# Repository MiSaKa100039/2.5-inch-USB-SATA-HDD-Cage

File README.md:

# ***2.5寸USB-SATA硬盘笼***

## <u>视频链接:[B站视频--功能演示及介绍](https://www.bilibili.com/video/BV1YCw5eoERG/?vd_source=5028cf5016d7ed990ad38551eb4883cf)</u>

## 项目简介:

本项目采用JMS578作为usb-sata桥,JMB575端口倍增的方案,实现usb到多个sata硬盘的通信

## 项目参数:

DC12v电源输入,jms578内置3.3v的ldo和buck控制器,因此只需考虑jmb575的3.3v和1.2v电压供电.
12v输入进来后通过tps54335a降压到5v,再使用mp9148双路buck降压输出3.3和1.2给jmb575供电

但是考虑到tps54335a的封装有点不好焊接,隧将其改为了中兴zxdn10的电源模块
和主机间连接采用Type-B接口,相对来说更为牢固.接口速度为USB3.0 5Gpbs,但是usb后面级联sata的方案对于硬盘的随机读写性能有较大的损失,所以对此在意的可以考虑其他方案(机械硬盘用户无视此条)

## 注意事项

1.在usb接口和dc电源接口的地方,请用钳子剪掉突出来的引脚,避免接触到硬盘.

2.先焊接电源部分,上电电压正常后再焊接芯片,以免烧毁芯片

3.jms578的晶振为30mhz,jmb575为25mhz

4.固件默认休眠时间为10min,若需更长时间或者关闭休眠,可以使用附件中的软件修改

5.由于最后一次修改工程后没能保存,所以附件中的ib0m和实际有区别,就是风扇接口位置不同.

6.电源功率的大小取决于你的硬盘功率

7.flash大部分都兼容,不确定就买p25d40h,便宜好用.

## 组装流程

背后的散热风扇为12v5010的风扇,主板上有一颗电阻位,可以选择合适大小的电阻来调节风扇转速,一般情况下直接短接即可

## 实物图

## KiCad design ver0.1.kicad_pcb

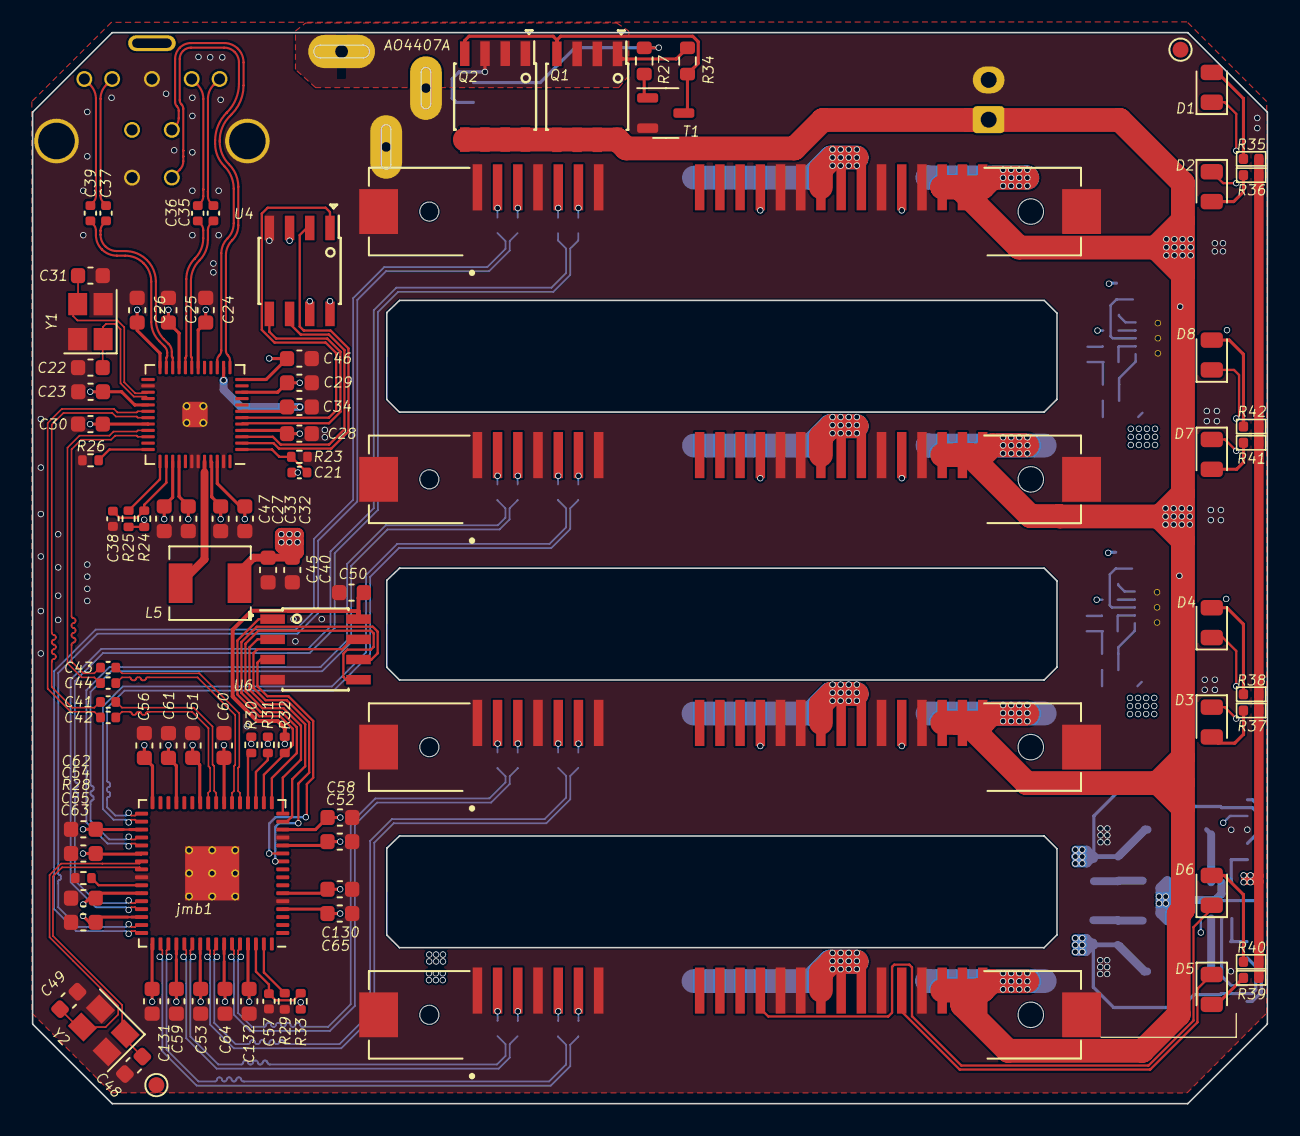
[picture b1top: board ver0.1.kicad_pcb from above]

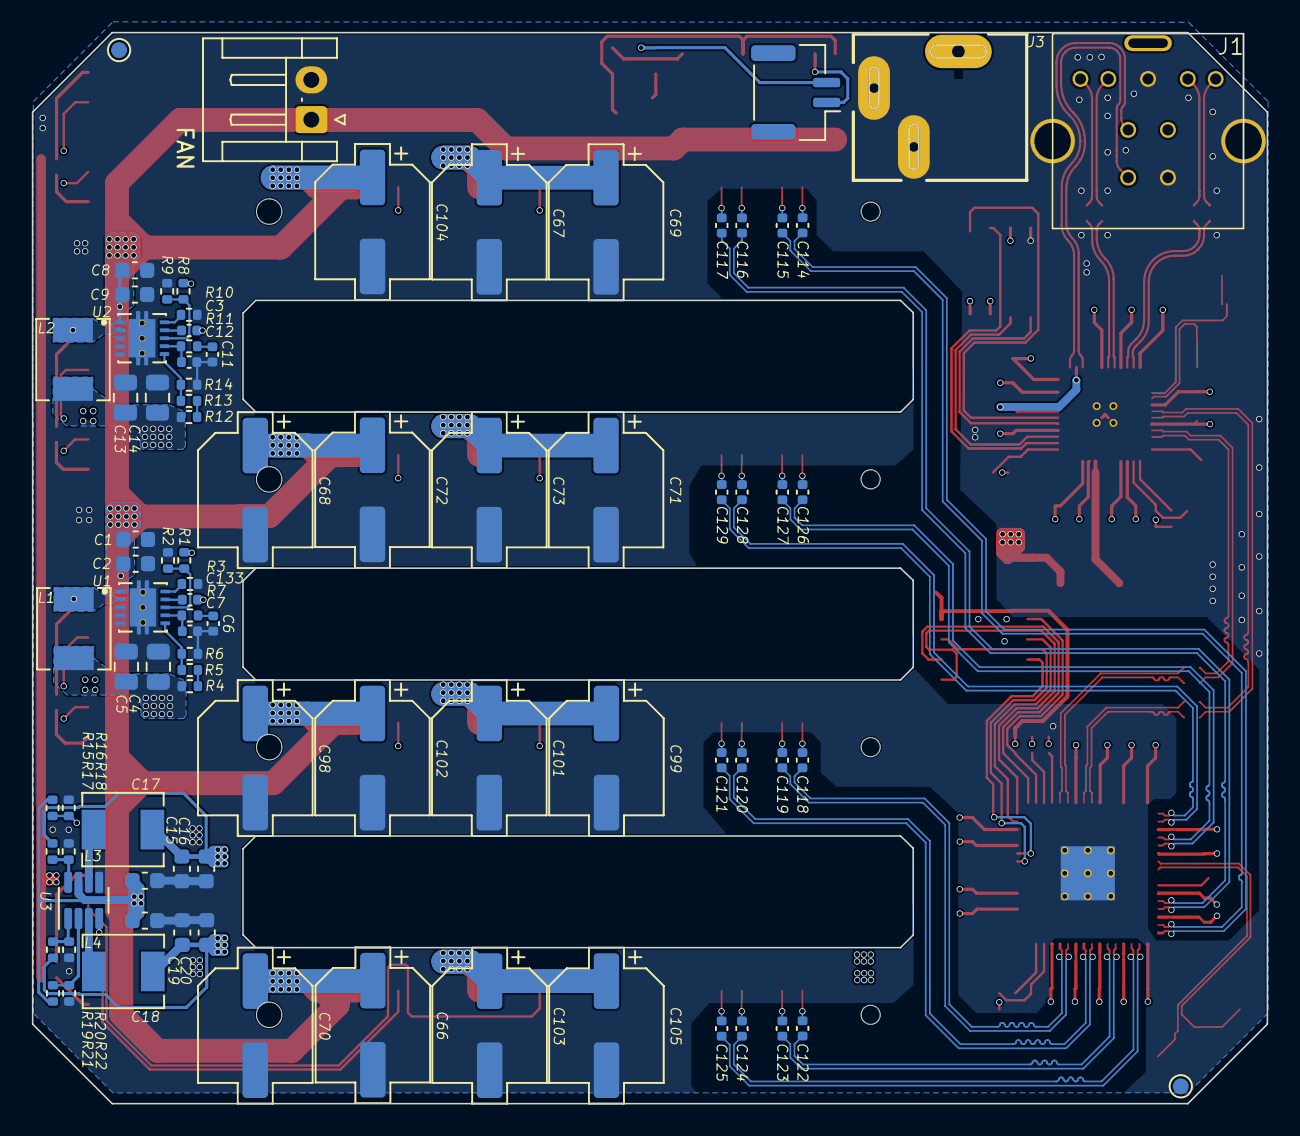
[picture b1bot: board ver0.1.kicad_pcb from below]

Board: 4 copper layers, 77.6 x 67.3 mm, 178 parts (86 on the bottom side), 124 nets.

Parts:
C1, C8, C15, C16, C19, C20, C40: 10uF; C_0603_1608Metric
C2, C9, C45: 0.1uF; C_0603_1608Metric
C3, C133: 0.1uF; C_0402_1005Metric
C4, C5, C13, C14: 47uF; C_0805_2012Metric
C6, C11: 0.012uF; C_0402_1005Metric
C7, C12: 120pF; C_0402_1005Metric
C17, C18: 22uF; C_0603_1608Metric
C21, C38, C57: 1uF; C_0402_1005Metric
C22, C31: 33pF; C_0603_1608Metric
C23, C24, C25, C26, C27, C28, C29, C30, C32, C33, C34, C46, C47, C50, C51, C52, C53, C54, C55, C56, C58, C59, C60, C61, C62, C63, C64, C65, C130, C131, C132: 100nF; C_0603_1608Metric
C35, C36: 100nF; C_0402_1005Metric
C37, C39: 0R; C_0402_1005Metric
C41, C42, C43, C44, C114, C115, C116, C117, C118, C119, C120, C121, C122, C123, C124, C125, C126, C127, C128, C129: 10nF; C_0402_1005Metric
C48, C49: 25pF; C_0603_1608Metric
C66, C67, C68, C69, C70, C71, C72, C73: 270uF; CP_Elec_6.3x5.4
C98, C99, C101, C102, C103, C104, C105: 22uF; CP_Elec_6.3x5.3
D1, D2, D3, D4, D5, D6, D7, D8: LED; LED_0805_2012Metric
FAN: fan2; JST_EH_S2B-EH_1x02_P2.50mm_Horizontal
FID1, FID2, FID3, FID4: Fiducial; TestPoint_Pad_D1.0mm
J1: USB 3.1 B; USB B 母座 直立
J2: SWITCH; JST_GH_BM02B-GHS-TBT_1x02-1MP_P1.25mm_Vertical
J3: dc 5.5mm; DC socket 5.5mm
J4, J5, J6, J7: SATA硬盘插头; SATA 29pin smd
L1, L2: 15uH; L_Chilisin_BMRA00040420
L3: 1uH; L_Chilisin_BMRA00040420
L4: 2uH; L_Chilisin_BMRA00040420
L5: 4.7uH; L_Chilisin_BMRA00040420
Q1, Q2: AO4407A; SOIC-8_3.9x4.9mm_Pitch1.27mm
R1, R8: 220k; R_0402_1005Metric
R2, R9: 43.2K; R_0402_1005Metric
R3, R10: 143K; R_0402_1005Metric
R4, R12: 51.1R; R_0402_1005Metric
R5, R13, R15, R21: 100k; R_0402_1005Metric
R6, R14: 19.1K; R_0402_1005Metric
R7, R11: 3.74K; R_0402_1005Metric
R16, R22: 43k; R_0402_1005Metric
R17, R19: 600K; R_0402_1005Metric
R18: 712K; R_0402_1005Metric
R20: 140K; R_0402_1005Metric
R23: 100K; R_0402_1005Metric
R24: 330K; R_0402_1005Metric
R25, R29, R30, R31, R32: 4.7K; R_0402_1005Metric
R26: 12K; R_0402_1005Metric
R27: 200Re; R_0603_1608Metric
R28: 12k; R_0402_1005Metric
R33: 10k; R_0402_1005Metric
R34: 4k; R_0603_1608Metric
R35, R36, R37, R38, R39, R40, R41, R42: 2k; R_0402
T1: T-BJT-NPN; SOT-23-3
U1, U2: TPS54335A; TPS54335ADRCR
U3: SOT-23-8
U4, U6: SOIC-8_3.9x4.9mm_Pitch1.27mm
U5: QFN-48-1EP_6x6mm_P0.4mm_EP4.2x4.2mm_ThermalVias
Y1, Y2: Crystal_GND24_Small; Crystal_SMD_Abracon_ABM8AIG-4Pin_3.2x2.5mm
jmb1: QFN-64-1EP_9x9mm_P0.5mm_EP3.4x3.4mm_ThermalVias

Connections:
+1V2: C15.2, C16.2, C58.2, C59.2, C60.2, C61.2, C62.2, C63.2, C64.2, C65.2, L3.1, R17.2, jmb1.4 (DV1.2), jmb1.14 (DV1.2), jmb1.23 (AV1.2), jmb1.29 (AV1.2), jmb1.35 (AV1.2), jmb1.46 (AV1.2), jmb1.52 (AV1.2), jmb1.58 (AV1.2)
+3V3: C19.2, C20.2, C50.2, C51.2, C52.2, C53.2, C54.2, C55.2, C56.2, C130.2, C131.2, C132.2, L4.2, R19.2, R30.2, R31.2, R32.2, R33.2, R35.1, R36.1, R37.1, R38.1, R39.1, R40.1, R41.1, R42.1, U6.8 (VCC), jmb1.6 (DV3.3), jmb1.12 (DV3.3), jmb1.26 (AV3.3), jmb1.32 (AV3.3), jmb1.38 (AV3.3), jmb1.43 (AV3.3), jmb1.49 (AV3.3), jmb1.55 (AV3.3), jmb1.61 (AV3.3)
+5V: C4.1, C5.1, C13.1, C14.1, C17.2, C18.2, C67.1, C69.1, C71.1, C73.1, C99.1, C101.1, C103.1, C105.1, J4.P7, J4.P8, J4.P9, J5.P7, J5.P8, J5.P9, J6.P7, J6.P8, J6.P9, J7.P7, J7.P8, J7.P9, L1.2, L2.2, R4.1, R12.1, R15.2, R21.2, U3.7 (IN)
/AGPIO0: U6.6 (SCLK), jmb1.17 (ZGPIO0)
/AGPIO1: U6.5 (SI), jmb1.16 (ZGPIO1)
/AGPIO2: U6.2 (SO), jmb1.15 (ZGPIO2)
/AGPIO3: U6.3 (WP#), jmb1.11 (ZGPIO3)
/AGPIO4: U6.7 (HOLD#), jmb1.10 (ZGPIO4)
/AGPIO12: R29.1, jmb1.63 (ZGPIO12)
/AGPIO13: R31.1, jmb1.19 (ZGPIO13)
/AGPIO14: R32.1, U6.1 (CS#), jmb1.18 (ZGPIO14)
/ARESETn: C57.1, R33.1, jmb1.62 (XRSTN)
/AREXT: R28.1, jmb1.42 (AREXT)
/ARXN0: C116.2, jmb1.45 (ARXN0)
/ARXN1: C120.2, jmb1.57 (ARXN1)
/ARXN2: C124.2, jmb1.51 (ARXN2)
/ARXN3: C128.2, jmb1.34 (ARXN3)
/ARXP0: C117.2, jmb1.44 (ARXP0)
/ARXP1: C121.2, jmb1.56 (ARXP1)
/ARXP2: C125.2, jmb1.50 (ARXP2)
/ARXP3: C129.2, jmb1.33 (ARXP3)
/ATESTn: R30.1, jmb1.20 (XTSTN)
/ATXN0: C115.2, jmb1.47 (ATXN0)
/ATXN1: C119.2, jmb1.59 (ATXN1)
/ATXN2: C123.2, jmb1.53 (ATXN2)
/ATXN3: C127.2, jmb1.36 (ATXN3)
/ATXP0: C114.2, jmb1.48 (ATXP0)
/ATXP1: C118.2, jmb1.60 (ATXP1)
/ATXP2: C122.2, jmb1.54 (ATXP2)
/ATXP3: C126.2, jmb1.37 (ATXP3)
/AXIN: C49.1, Y2.3, jmb1.39 (AXIN)
/AXOUT: C48.2, Y2.1, jmb1.40 (AXOUT)
/DAS1: D2.1 (K), J4.P11
/DAS2: D3.1 (K), J5.P11
/DAS3: D5.1 (K), J6.P11
/DAS4: D7.1 (K), J7.P11
/GPIO0: U4.2 (SO), U5.2 (GPIO0)
/GPIO1: U4.6 (SCLK), U5.3 (GPIO1)
/GPIO2: U4.5 (SI), U5.5 (GPIO2)
/GPIO3: U4.1 (CS#), U5.6 (GPIO3)
/HOT1: D1.1 (K), J4.P4
/HOT2: D4.1 (K), J5.P4
/HOT3: D6.1 (K), J6.P4
/HOT4: D8.1 (K), J7.P4
/HSD0+: J1.3 (D+), U5.15 (DP)
/HSD0-: J1.2 (D-), U5.13 (DM)
/LXO: L5.1, U5.44 (LXO)
/RST: C38.1, R24.2, U5.38 (RST#)
/RX_N: C41.1, U5.31 (RXN)
/RX_P: C42.1, U5.30 (RXP)
/SSRX0+: C39.1, J1.9 (STDB_SSRX+)
/SSRX0-: C37.1, J1.8 (STDB_SSRX-)
/SSTX0+: C35.1, J1.5 (STDB_SSTX-)
/SSTX0-: C36.1, J1.6 (STDB_SSTX+)
/TX_N: C44.1, U5.33 (TXN)
/TX_P: C43.1, U5.34 (TXP)
/XIN: C22.2, U5.28 (XIN), Y1.1
/XOUT: C31.1, U5.27 (XOUT), Y1.3
/cap-SSRX1+: C39.2, U5.23 (SSRXP)
/cap-SSRX1-: C37.2, U5.22 (SSRXN)
/cap-SSTX1+: C36.2, U5.20 (SSTXP)
/cap-SSTX1-: C35.2, U5.19 (SSTXN)
/net-RX_N: C41.2, jmb1.24 (ATXN5)
/net-RX_P: C42.2, jmb1.25 (ATXP5)
/net-TX_N: C44.2, jmb1.22 (ARXN5)
/net-TX_P: C43.2, jmb1.21 (ARXP5)
/vout1.2: C23.2, C24.2, C25.2, C26.2, C27.2, C28.2, C29.2, C30.2, C40.2, C45.2, L5.2, U5.4 (VCCK), U5.10 (VCCK), U5.18 (AVDDL), U5.21 (AVDDL), U5.24 (AVDDL), U5.29 (AVDDL), U5.32 (AVDDL), U5.40 (VCCK)
/vout3.3: C21.1, C32.2, C33.2, C34.2, R24.1, R25.2, U4.3 (WP#), U4.7 (HOLD#), U4.8 (VCC), U5.7 (VCCO), U5.14 (AV33O), U5.39 (VCCO), U5.46 (MODE0)
GND: C1.1, C2.1, C4.2, C5.2, C6.2, C7.2, C8.1, C9.1, C11.2, C12.2, C13.2, C14.2, C15.1, C16.1, C17.1, C18.1, C19.1, C20.1, C22.1, C23.1, C24.1, C25.1, C26.1, C27.1, C28.1, C29.1, C30.1, C31.2, C32.1, C33.1, C34.1, C38.2, C40.1, C45.1, C46.1, C47.1, C48.1, C49.2, C50.1, C51.1, C52.1, C53.1, C54.1, C55.1, C56.1, C57.2, C58.1, C59.1, C60.1, C61.1, C62.1, C63.1, C64.1, C65.1, C66.2, C67.2, C68.2, C69.2, C70.2, C71.2, C72.2, C73.2, C98.2, C99.2, C101.2, C102.2, C103.2, C104.2, C105.2, C130.1, C131.1, C132.1, FAN.2, J1.4 (GND), J1.7 (GND_DRAIN), J1.S1, J1.S2, J3.2, J3.3, J4.P5, J4.P6, J4.P10, J4.P12, J4.S1, J4.S4, J4.S7, J4.SH1 (SHIELD), J4.SH2 (SHIELD), J5.P5, J5.P6, J5.P10, J5.P12, J5.S1, J5.S4, J5.S7, J5.SH1 (SHIELD), J5.SH2 (SHIELD), J6.P5, J6.P6, J6.P10, J6.P12, J6.S1, J6.S4, J6.S7, J6.SH1 (SHIELD), J6.SH2 (SHIELD), J7.P5, J7.P6, J7.P10, J7.P12, J7.S1, J7.S4, J7.S7, J7.SH1 (SHIELD), J7.SH2 (SHIELD), R2.2, R3.2, R6.2, R9.2, R10.2, R14.2, R16.1, R18.1, R20.1, R22.1, R23.2, R26.2, R28.2, R29.2, T1.2 (B), U1.3 (GND), U1.4 (GND), U1.5 (GND), U1.11 (GND), U2.3 (GND), U2.4 (GND), U2.5 (GND), U2.11 (GND), U3.5 (GND), U4.4 (GND), U5.26 (NC), U5.42 (MODE1), U5.43 (GND), U5.47 (NC), U5.49 (GND), U6.4 (GND), Y1.2, Y1.4, Y2.2, Y2.4, jmb1.5 (DGND), jmb1.13 (DGND), jmb1.41 (AGND), jmb1.65 (GND)
unnamed: C6.1, R7.2
unnamed: C11.1, R11.2
unnamed: C114.1, J4.S2
unnamed: C115.1, J4.S3
unnamed: C116.1, J4.S5
unnamed: C117.1, J4.S6
unnamed: C118.1, J5.S2
unnamed: C119.1, J5.S3
unnamed: C120.1, J5.S5
unnamed: C121.1, J5.S6
unnamed: C122.1, J6.S2
unnamed: C123.1, J6.S3
unnamed: C124.1, J6.S5
unnamed: C125.1, J6.S6
unnamed: C126.1, J7.S2
unnamed: C127.1, J7.S3
unnamed: C128.1, J7.S5
unnamed: C129.1, J7.S6
unnamed: D1.2 (A), R35.2
unnamed: D2.2 (A), R36.2
unnamed: D3.2 (A), R37.2
unnamed: D4.2 (A), R38.2
unnamed: D5.2 (A), R39.2
unnamed: D6.2 (A), R40.2
unnamed: D7.2 (A), R41.2
unnamed: D8.2 (A), R42.2
unnamed: J2.2, R27.1
unnamed: Q1.4 (G), Q2.4 (G), R34.2, T1.3 (E)
unnamed: R4.2, R5.1
unnamed: R12.2, R13.1
unnamed: R27.2, T1.1 (C)
unnamed: C133.1, U1.9 (BOOT)
unnamed: C7.1, R7.1, U1.7 (COMP)
unnamed: R1.2, R2.1, U1.8 (EN)
unnamed: C133.2, L1.1, U1.2 (PH)
unnamed: R3.1, U1.10 (RT)
unnamed: C3.1, U2.9 (BOOT)
unnamed: C12.1, R11.1, U2.7 (COMP)
unnamed: R8.2, R9.1, U2.8 (EN)
unnamed: C3.2, L2.1, U2.2 (PH)
unnamed: R10.1, U2.10 (RT)
unnamed: R15.1, R16.2, U3.4 (EN1)
unnamed: R21.1, R22.2, U3.2 (EN2)
unnamed: R17.1, R18.2, U3.8 (FB1)
unnamed: R19.1, R20.2, U3.1 (FB2)
unnamed: L3.2, U3.6 (SW1)
unnamed: L4.1, U3.3 (SW2)
unnamed: R26.1, U5.36 (REXT)
unnamed: C21.2, R23.1, U5.1 (TME)
unnamed: R25.1, U5.37 (UAO/GPIO8)
VBUS: C46.2, C47.2, J1.1 (VBUS), U5.12 (VBUS), U5.45 (VREG_IN)
VDC: J2.1, J3.1, Q1.1 (S), Q1.2 (S), Q1.3 (S), Q2.1 (S), Q2.2 (S), Q2.3 (S), R34.1
Vin_12V: C1.2, C2.2, C8.2, C9.2, C66.1, C68.1, C70.1, C72.1, C98.1, C102.1, C104.1, FAN.1, J4.P13, J4.P14, J4.P15, J5.P13, J5.P14, J5.P15, J6.P13, J6.P14, J6.P15, J7.P13, J7.P14, J7.P15, Q1.5 (D), Q1.6 (D), Q1.7 (D), Q1.8 (D), Q2.5 (D), Q2.6 (D), Q2.7 (D), Q2.8 (D), R1.1, R8.1, U1.1 (VIN), U2.1 (VIN)
Vsense-A: R5.2, R6.1, U1.6 (VSENSE)
Vsense-B: R13.2, R14.1, U2.6 (VSENSE)

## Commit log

2025-01-22 README
2025-01-22 rule
2025-01-22 Test
2025-01-22 Rename 2.5-inch-USB-SATA-HDD-Cage.md to README.md
2025-01-22 README.md
2025-08-01 ver1.4
